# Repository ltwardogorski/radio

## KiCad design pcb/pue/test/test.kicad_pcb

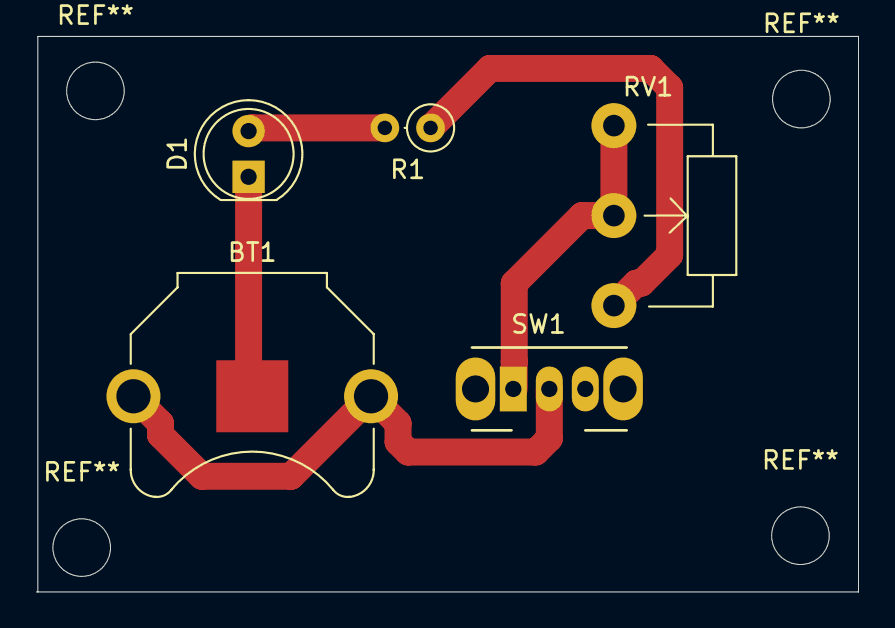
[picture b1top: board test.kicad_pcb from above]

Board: 2 copper layers, 45.7 x 30.9 mm, 5 parts (0 on the bottom side), 5 nets.

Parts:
BT1: 3V litowa; Keystone_3001_1x12mm-CoinCell
D1: czerwona; LED_D5.0mm
R1: 220; R_Axial_DIN0207_L6.3mm_D2.5mm_P2.54mm_Vertical
RV1: 10k; Potentiometer_WirePads
SW1: SW_SPDT; SW_CuK_OS102011MA1QN1_SPDT_Angled

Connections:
GND: BT1.2, D1.1
unnamed: BT1.1, SW1.2
unnamed: D1.2, R1.2
unnamed: R1.1, RV1.3
unnamed: RV1.1, RV1.2, SW1.1
